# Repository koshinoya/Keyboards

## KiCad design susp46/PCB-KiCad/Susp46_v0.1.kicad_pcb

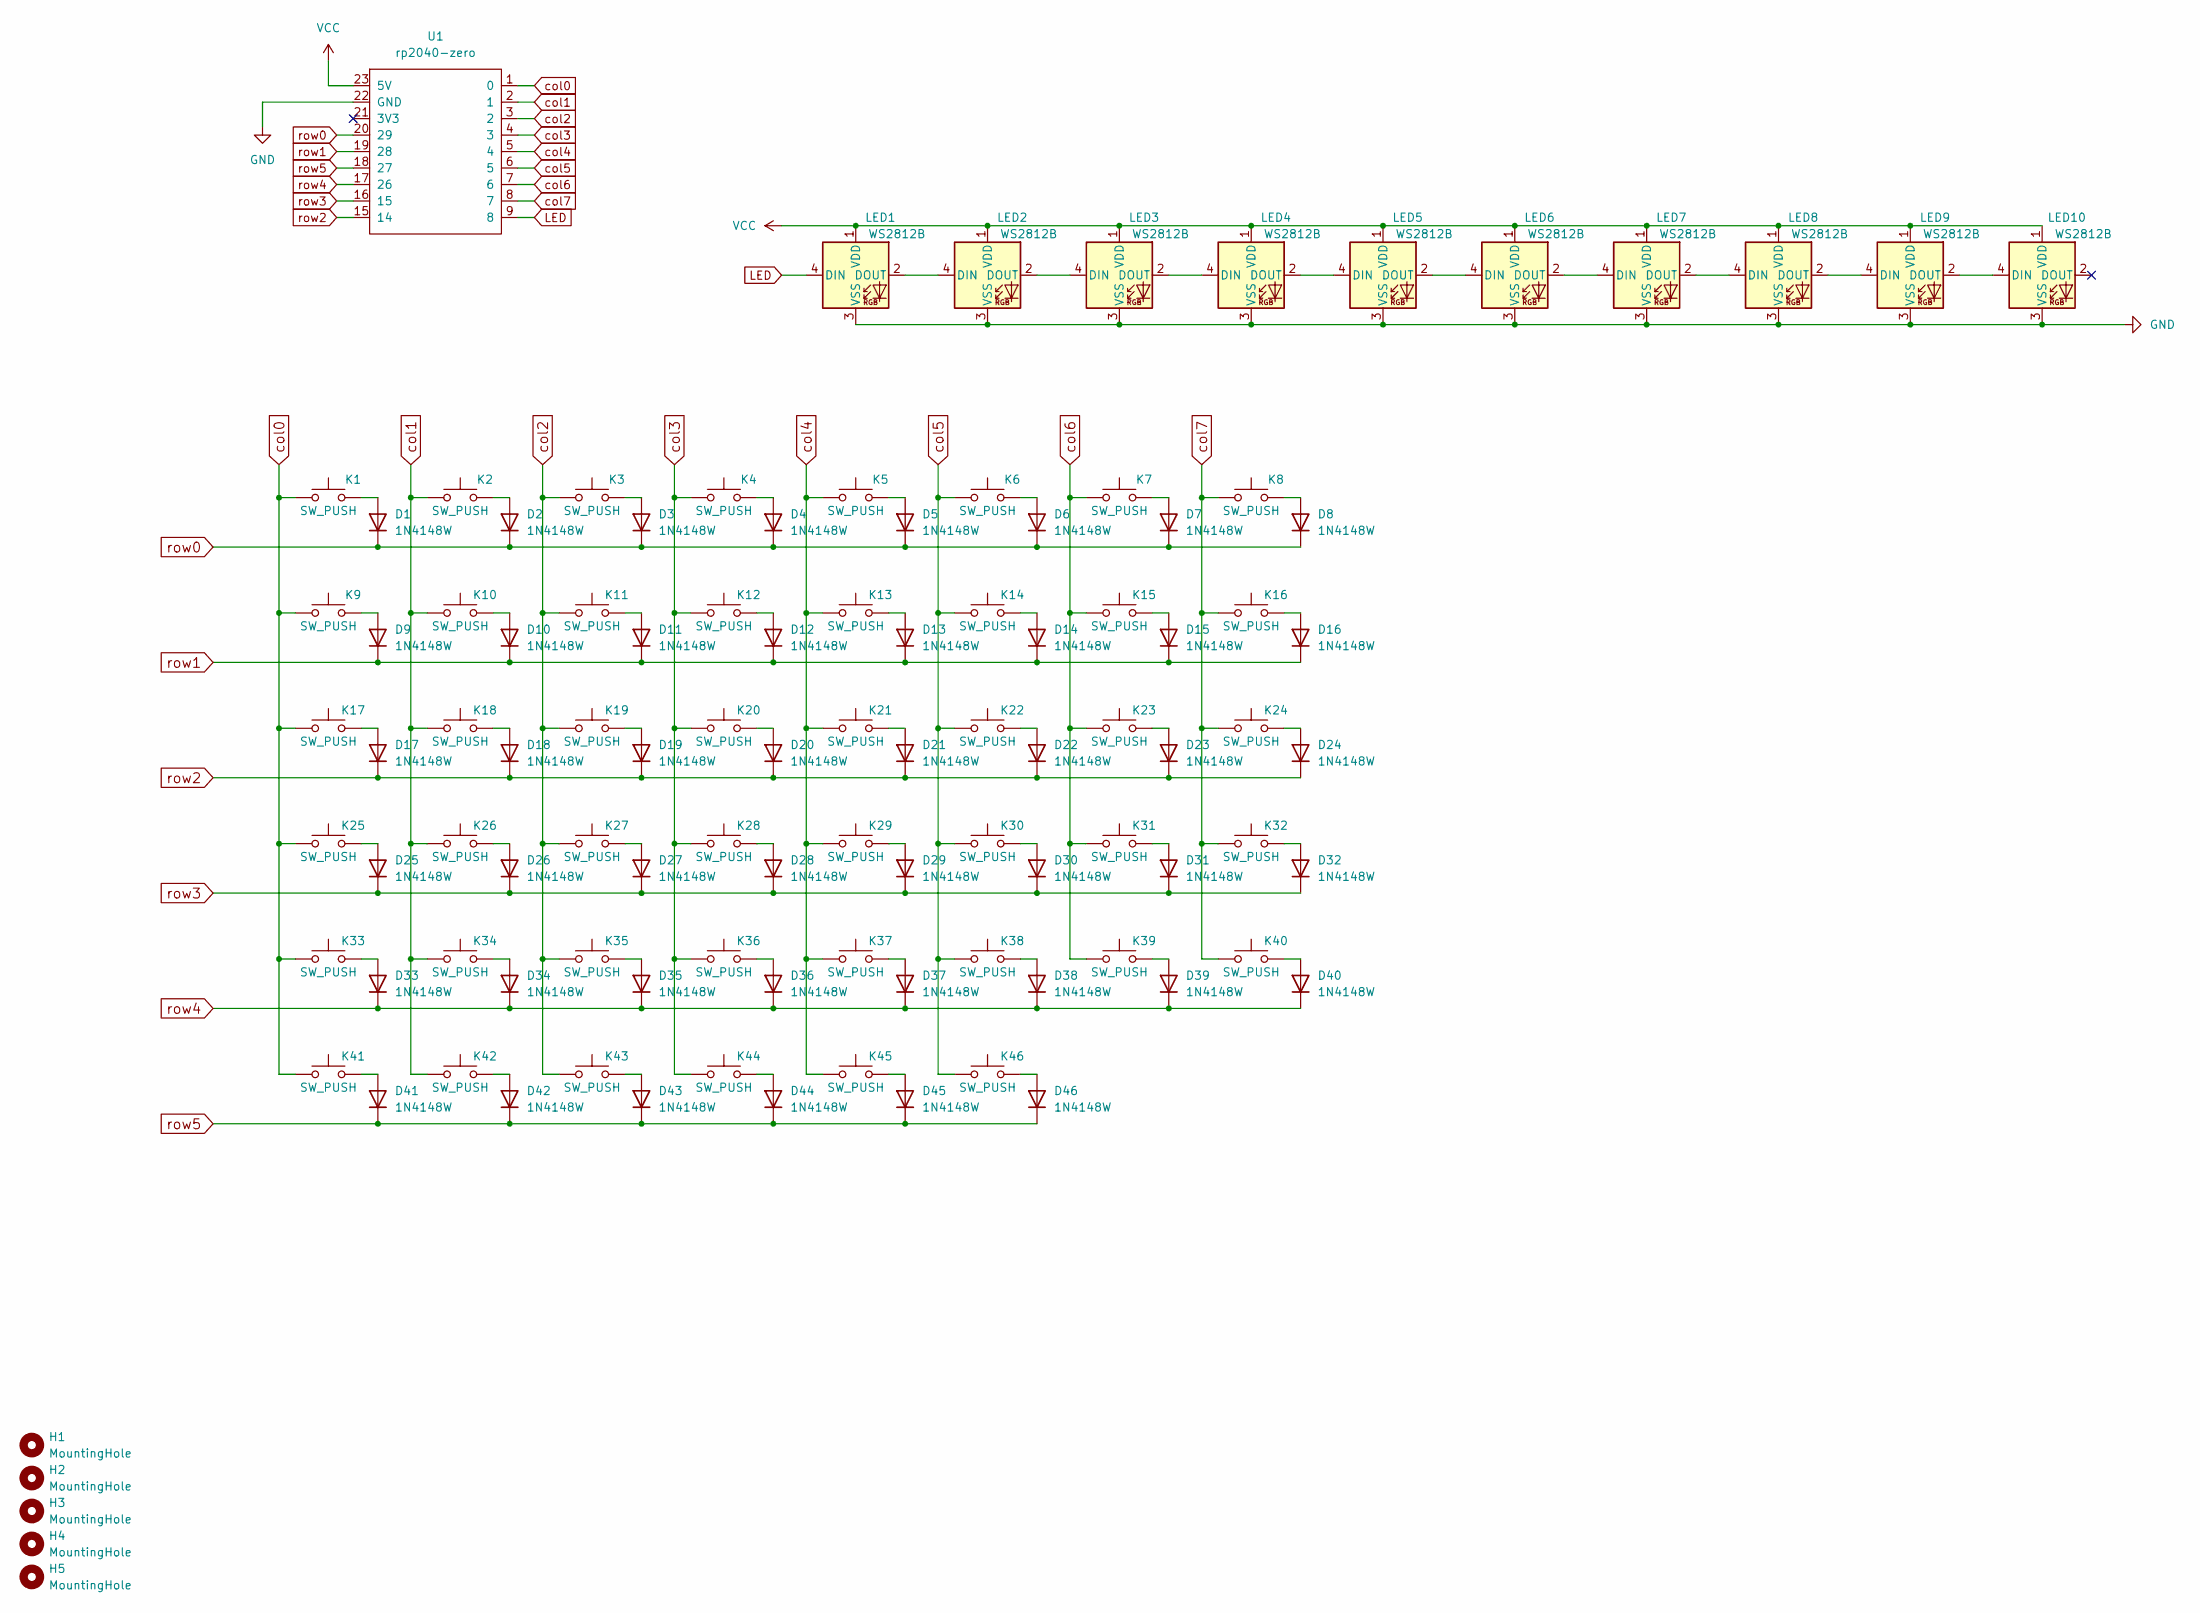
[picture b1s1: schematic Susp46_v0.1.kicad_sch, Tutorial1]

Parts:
D1, D2, D3, D4, D5, D6, D7, D8, D9, D10, D11, D12, D13, D14, D15, D16, D17, D18, D19, D20, D21, D22, D23, D24, D25, D26, D27, D28, D29, D30, D31, D32, D33, D34, D35, D36, D37, D38, D39, D40, D41, D42, D43, D44, D45, D46: 1N4148W; D_SOD-123
H1, H2, H3, H4, H5: MountingHole; MountingHole_2.2mm_M2_Pad_TopBottom
K1, K2, K3, K4, K5, K6, K7, K8, K9, K10, K11, K12, K13, K15, K16, K17, K18, K19, K20, K21, K22, K23, K24, K27, K28, K29, K30, K31, K32, K33, K34, K35, K36, K44, K45, K46: SW_PUSH; SW_Cherry_MX_1.00u_PCB
K14, K37, K38, K39, K40, K43: SW_PUSH; SW_Cherry_MX_1.25u_PCB
K25, K26: SW_PUSH; SW_Cherry_MX_1.75u_PCB
K41: SW_PUSH; SW_Cherry_MX_2.25u_PCB
K42: SW_PUSH; SW_Cherry_MX_2.75u_PCB
LED1, LED2, LED3, LED4, LED5, LED6, LED7, LED8, LED9, LED10: WS2812B; LED_WS2812B_PLCC4_5.0x5.0mm_P3.2mm
U1: rp2040-zero; rp2040-zero-tht-5Pads-Less

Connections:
GND: LED1.3 (VSS), LED2.3 (VSS), LED3.3 (VSS), LED4.3 (VSS), LED5.3 (VSS), LED6.3 (VSS), LED7.3 (VSS), LED8.3 (VSS), LED9.3 (VSS), LED10.3 (VSS), U1.22 (GND)
LED: LED1.4 (DIN), U1.9 (8)
unnamed: D1.2 (A), K1.2
unnamed: D2.2 (A), K2.2
unnamed: D3.2 (A), K3.2
unnamed: D4.2 (A), K4.2
unnamed: D5.2 (A), K5.2
unnamed: D6.2 (A), K6.2
unnamed: D7.2 (A), K7.2
unnamed: D8.2 (A), K8.2
unnamed: D9.2 (A), K9.2
unnamed: D10.2 (A), K10.2
unnamed: D11.2 (A), K11.2
unnamed: D12.2 (A), K12.2
unnamed: D13.2 (A), K13.2
unnamed: D14.2 (A), K14.2
unnamed: D15.2 (A), K15.2
unnamed: D16.2 (A), K16.2
unnamed: D17.2 (A), K17.2
unnamed: D18.2 (A), K18.2
unnamed: D19.2 (A), K19.2
unnamed: D20.2 (A), K20.2
unnamed: D21.2 (A), K21.2
unnamed: D22.2 (A), K22.2
unnamed: D23.2 (A), K23.2
unnamed: D24.2 (A), K24.2
unnamed: D25.2 (A), K25.2
unnamed: D26.2 (A), K26.2
unnamed: D27.2 (A), K27.2
unnamed: D28.2 (A), K28.2
unnamed: D29.2 (A), K29.2
unnamed: D30.2 (A), K30.2
unnamed: D31.2 (A), K31.2
unnamed: D32.2 (A), K32.2
unnamed: D33.2 (A), K33.2
unnamed: D34.2 (A), K34.2
unnamed: D35.2 (A), K35.2
unnamed: D36.2 (A), K36.2
unnamed: D37.2 (A), K37.2
unnamed: D38.2 (A), K38.2
unnamed: D39.2 (A), K39.2
unnamed: D40.2 (A), K40.2
unnamed: D41.2 (A), K41.2
unnamed: D42.2 (A), K42.2
unnamed: D43.2 (A), K43.2
unnamed: D44.2 (A), K44.2
unnamed: D45.2 (A), K45.2
unnamed: D46.2 (A), K46.2
unnamed: LED1.2 (DOUT), LED2.4 (DIN)
unnamed: LED2.2 (DOUT), LED3.4 (DIN)
unnamed: LED3.2 (DOUT), LED4.4 (DIN)
unnamed: LED4.2 (DOUT), LED5.4 (DIN)
unnamed: LED5.2 (DOUT), LED6.4 (DIN)
unnamed: LED6.2 (DOUT), LED7.4 (DIN)
unnamed: LED7.2 (DOUT), LED8.4 (DIN)
unnamed: LED8.2 (DOUT), LED9.4 (DIN)
unnamed: LED9.2 (DOUT), LED10.4 (DIN)
VCC: LED1.1 (VDD), LED2.1 (VDD), LED3.1 (VDD), LED4.1 (VDD), LED5.1 (VDD), LED6.1 (VDD), LED7.1 (VDD), LED8.1 (VDD), LED9.1 (VDD), LED10.1 (VDD), U1.23 (5V)
col0: K1.1, K9.1, K17.1, K25.1, K33.1, K41.1, U1.1 (0)
col1: K2.1, K10.1, K18.1, K26.1, K34.1, K42.1, U1.2 (1)
col2: K3.1, K11.1, K19.1, K27.1, K35.1, K43.1, U1.3 (2)
col3: K4.1, K12.1, K20.1, K28.1, K36.1, K44.1, U1.4 (3)
col4: K5.1, K13.1, K21.1, K29.1, K37.1, K45.1, U1.5 (4)
col5: K6.1, K14.1, K22.1, K30.1, K38.1, K46.1, U1.6 (5)
col6: K7.1, K15.1, K23.1, K31.1, K39.1, U1.7 (6)
col7: K8.1, K16.1, K24.1, K32.1, K40.1, U1.8 (7)
row0: D1.1 (K), D2.1 (K), D3.1 (K), D4.1 (K), D5.1 (K), D6.1 (K), D7.1 (K), D8.1 (K), U1.20 (29)
row1: D9.1 (K), D10.1 (K), D11.1 (K), D12.1 (K), D13.1 (K), D14.1 (K), D15.1 (K), D16.1 (K), U1.19 (28)
row2: D17.1 (K), D18.1 (K), D19.1 (K), D20.1 (K), D21.1 (K), D22.1 (K), D23.1 (K), D24.1 (K), U1.15 (14)
row3: D25.1 (K), D26.1 (K), D27.1 (K), D28.1 (K), D29.1 (K), D30.1 (K), D31.1 (K), D32.1 (K), U1.16 (15)
row4: D33.1 (K), D34.1 (K), D35.1 (K), D36.1 (K), D37.1 (K), D38.1 (K), D39.1 (K), D40.1 (K), U1.17 (26)
row5: D41.1 (K), D42.1 (K), D43.1 (K), D44.1 (K), D45.1 (K), D46.1 (K), U1.18 (27)

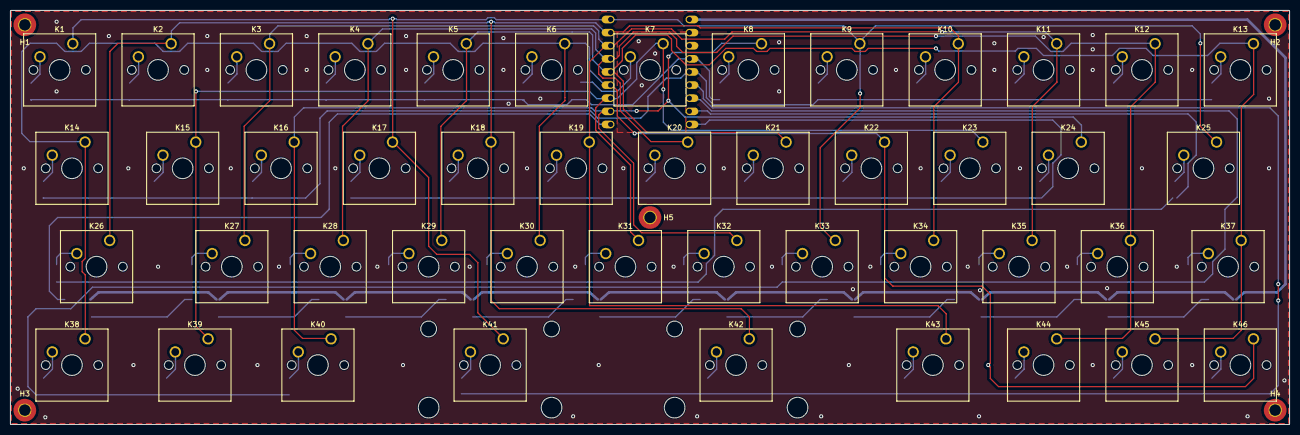
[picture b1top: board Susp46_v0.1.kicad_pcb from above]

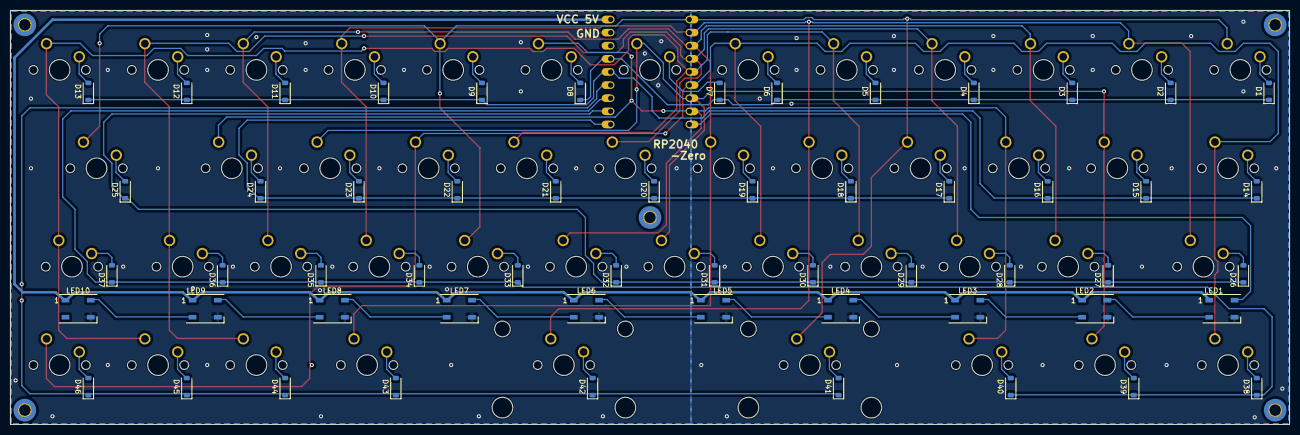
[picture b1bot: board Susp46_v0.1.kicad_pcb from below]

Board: 2 copper layers, 247.7 x 80.2 mm, 108 parts (56 on the bottom side), 72 nets.

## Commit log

2020-04-29 Add build guide for rect44
2020-04-29 update rect44 build guide
2020-04-29 deleted 2 files
2020-04-29 add jpg files
2020-04-30 Update build guide
2020-05-01 Modified Rect44 build guide
2020-05-05 Upload DXF data of Rect44 case
2020-08-16 Add build guide jp v1.2
2020-10-14 New file Rect44_build_guide_jp_v1.2.1.md
2021-01-18 Upload .json and .png files
    * rect44/img/road_json_btn.png
    * rect44/json/ansi_44key.json
    * rect44/json/ansi_47key.json
    * rect44/json/iso_48key.json
2021-01-18 Update build guide
    * Update rect44/Rect44_build_guide_jp_v1.2.1.md
    * Fix rect44/img/road_json_btn.png
2021-03-26 Correct build guide.
2022-01-23 Add PCB support
    Upload Rect44_build_guide_jp_v1.2.2.md and jpg files.
2022-01-23 Upload rect44/img/bt_plate_07.jpg
2022-03-15 New file Rect44_build_guide_en_v1.2.2.md
    Build guide English version.
    ver1.2.2
2022-03-28 New file
    Mod Rect44_build_guide_en_1.2.2.md
2024-05-05 Create LICENSE
2024-05-05 Add susp46
2024-05-05 modify rect44/data/dxf_jp.md
